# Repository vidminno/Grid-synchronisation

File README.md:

# Grid synchronisation

This repository contains an easy-to-implement grid synchronisation circuit.

## Content
- **Hardware**: KiCad schematic and layout design for isolated grid frequency acquisition.
- **Software**: Implementation for an STM32 Nucleo H755 for grid synchronisation.

## Functionality
The circuit uses opto-emulators (ISOM8710) for isolated detection of the mains zero crossing. A microcontroller analyses the signal edges to calculate the mains frequency and phase position.

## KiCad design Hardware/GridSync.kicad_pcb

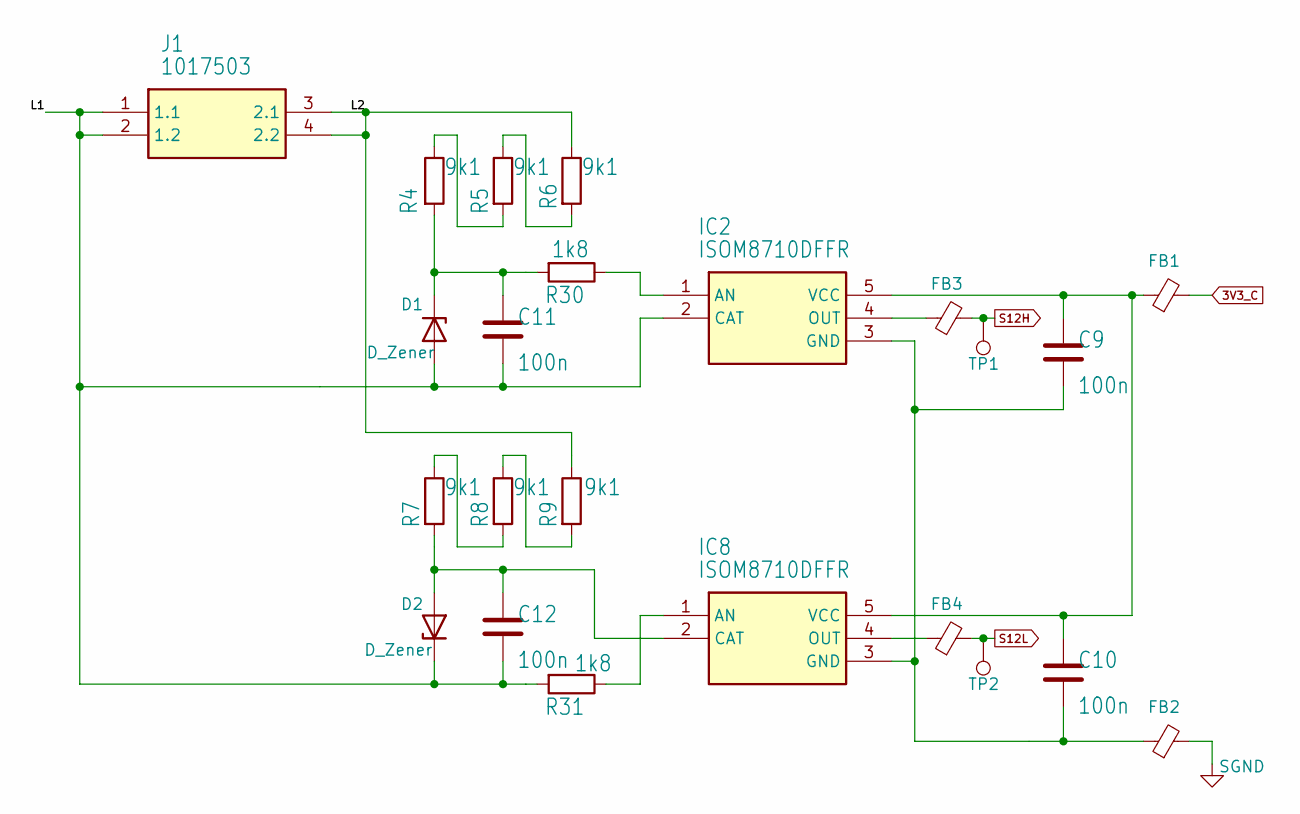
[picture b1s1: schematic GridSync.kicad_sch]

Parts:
C9, C10, C11, C12: 100n; C_0805_2012Metric_Pad1.18x1.45mm_HandSolder
D1, D2: D_Zener; D_SOD-323_HandSoldering
FB1, FB2, FB3, FB4: L_0805_2012Metric_Pad1.15x1.40mm_HandSolder
IC2, IC8: ISOM8710DFFR; Mouser Part Number 595-ISOM8710DFFR
J1: 1017503; Mouser Part Number 651-1017503
R4, R5, R6, R7, R8, R9: 9k1; R_1206_3216Metric_Pad1.30x1.75mm_HandSolder
R30, R31: 1k8; R_0805_2012Metric_Pad1.20x1.40mm_HandSolder
TP1, TP2: TestPoint; TestPoint_THTPad_D2.0mm_Drill1.0mm

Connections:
3V3_C: FB1.2
/L1: C11.2, C12.2, D1.2 (A), D2.1 (K), IC2.2 (CAT), J1.1 (1.1), J1.2 (1.2), R31.2
/L2: J1.3 (2.1), J1.4 (2.2), R6.1, R9.1
unnamed: C11.1, D1.1 (K), R4.2, R30.2
unnamed: C12.1, D2.2 (A), IC8.2 (CAT), R7.2
unnamed: IC2.1 (AN), R30.1
unnamed: C9.2, C10.2, FB2.1, IC2.3 (GND), IC8.3 (GND)
unnamed: FB3.1, IC2.4 (OUT)
unnamed: C9.1, C10.1, FB1.1, IC2.5 (VCC), IC8.5 (VCC)
unnamed: IC8.1 (AN), R31.1
unnamed: FB4.1, IC8.4 (OUT)
unnamed: R4.1, R5.2
unnamed: R5.1, R6.2
unnamed: R7.1, R8.2
unnamed: R8.1, R9.2
S12H: FB3.2, TP1.1
S12L: FB4.2, TP2.1
SGND: FB2.2

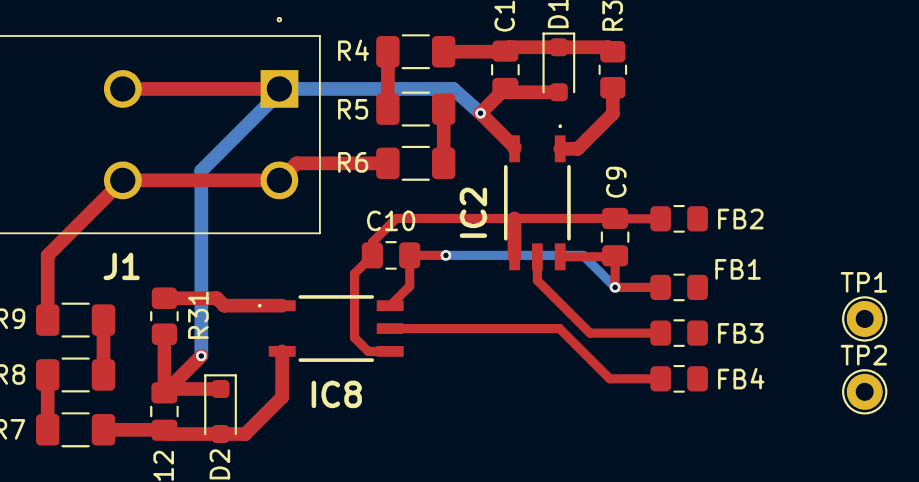
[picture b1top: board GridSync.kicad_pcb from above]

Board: 2 copper layers, 23 parts (0 on the bottom side), 16 nets.

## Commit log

2025-03-05 Add gitignore
2025-03-05 SW: Add STM Project
2025-03-05 SW: Basic CubeMX config
2025-03-05 SW: Launch M7 first and M4 afterwards
    A manual reset (button) must be performed after the launch
2025-03-05 SW: Add grid synchronisation
2025-03-05 HW: Add KiCad files
    Add KiCad schematic and board design approach
2025-03-05 Doc: Descripe basic HW and SW function
2025-03-05 Add licence and readme
